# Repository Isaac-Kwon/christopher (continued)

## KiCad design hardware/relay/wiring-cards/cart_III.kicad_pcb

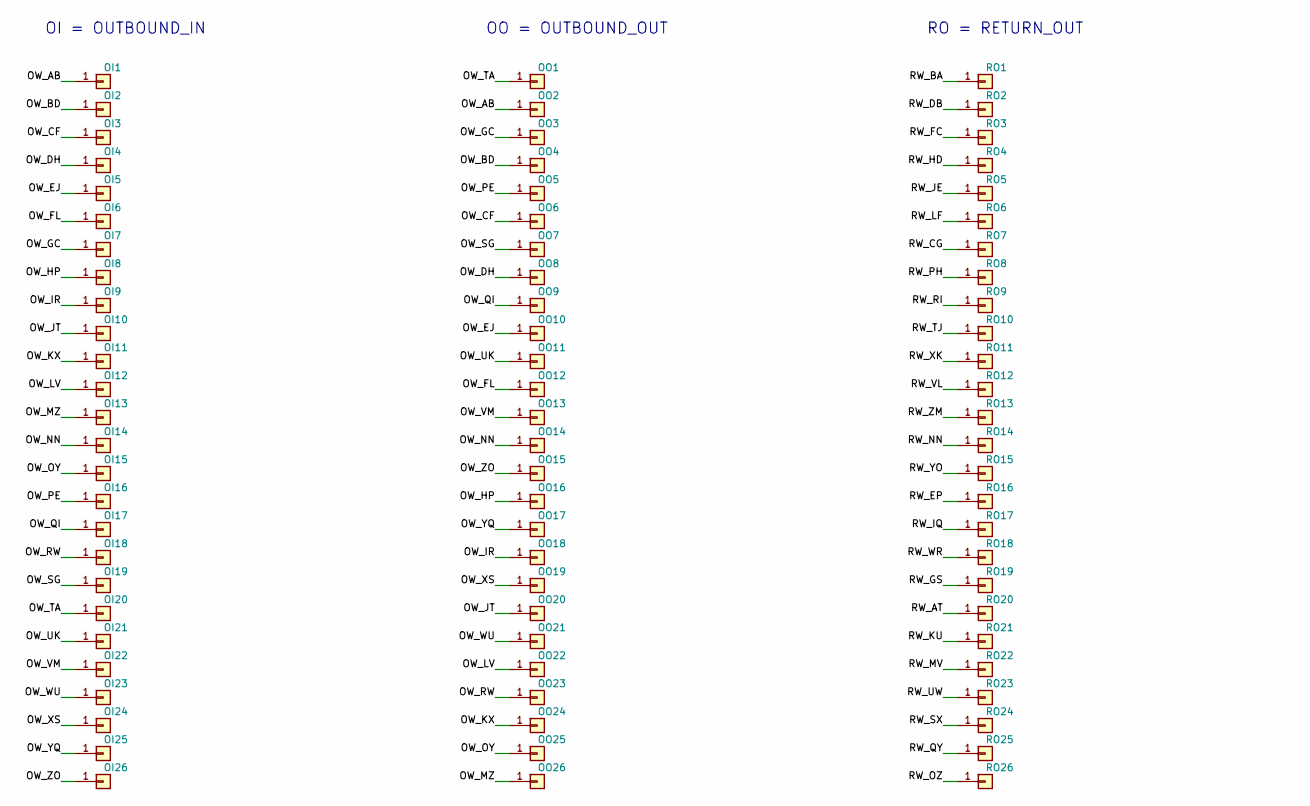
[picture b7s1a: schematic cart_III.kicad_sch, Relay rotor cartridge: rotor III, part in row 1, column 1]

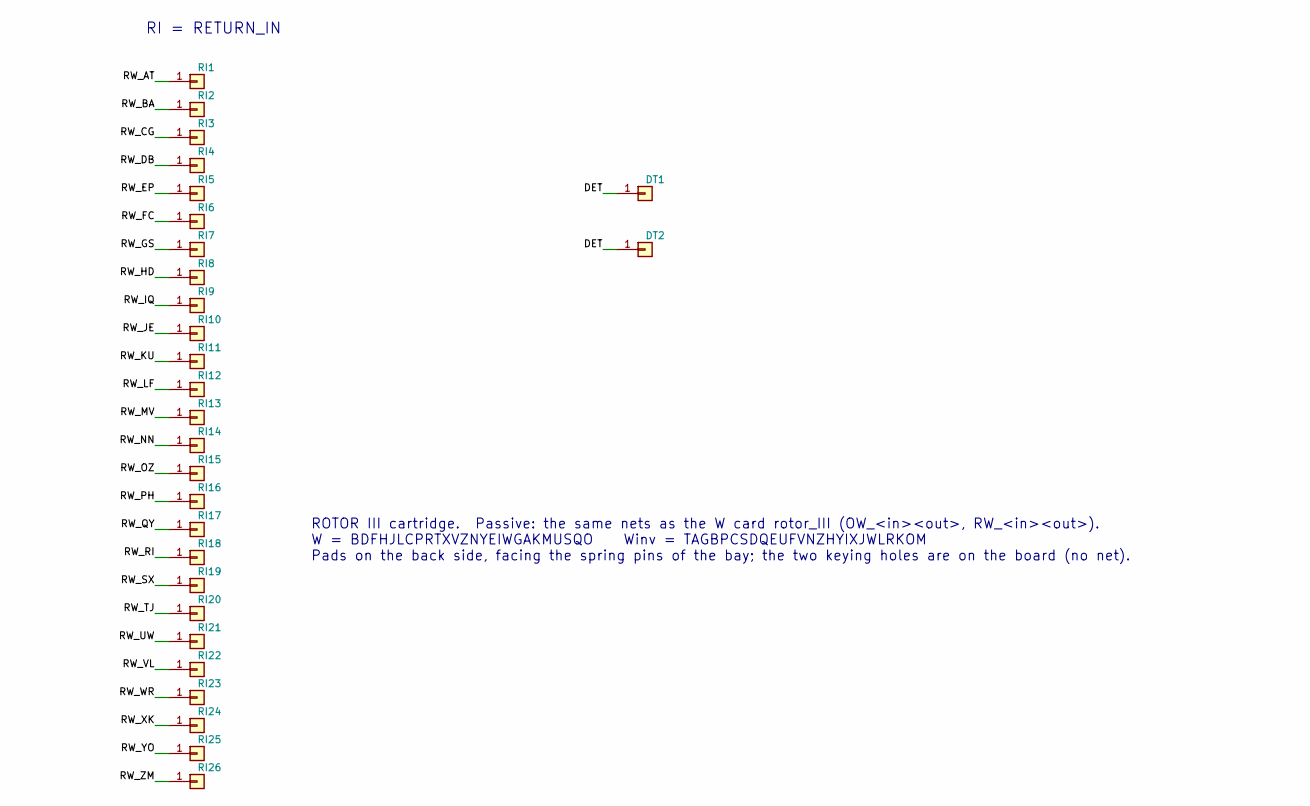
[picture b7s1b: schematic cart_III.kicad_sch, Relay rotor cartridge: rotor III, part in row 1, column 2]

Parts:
DT1: DETECT 1; CartridgePad_D1.8
DT2: DETECT 2; CartridgePad_D1.8
OI1: PAD OI A; CartridgePad_D1.8
OI2: PAD OI B; CartridgePad_D1.8
OI3: PAD OI C; CartridgePad_D1.8
OI4: PAD OI D; CartridgePad_D1.8
OI5: PAD OI E; CartridgePad_D1.8
OI6: PAD OI F; CartridgePad_D1.8
OI7: PAD OI G; CartridgePad_D1.8
OI8: PAD OI H; CartridgePad_D1.8
OI9: PAD OI I; CartridgePad_D1.8
OI10: PAD OI J; CartridgePad_D1.8
OI11: PAD OI K; CartridgePad_D1.8
OI12: PAD OI L; CartridgePad_D1.8
OI13: PAD OI M; CartridgePad_D1.8
OI14: PAD OI N; CartridgePad_D1.8
OI15: PAD OI O; CartridgePad_D1.8
OI16: PAD OI P; CartridgePad_D1.8
OI17: PAD OI Q; CartridgePad_D1.8
OI18: PAD OI R; CartridgePad_D1.8
OI19: PAD OI S; CartridgePad_D1.8
OI20: PAD OI T; CartridgePad_D1.8
OI21: PAD OI U; CartridgePad_D1.8
OI22: PAD OI V; CartridgePad_D1.8
OI23: PAD OI W; CartridgePad_D1.8
OI24: PAD OI X; CartridgePad_D1.8
OI25: PAD OI Y; CartridgePad_D1.8
OI26: PAD OI Z; CartridgePad_D1.8
OO1: PAD OO A; CartridgePad_D1.8
OO2: PAD OO B; CartridgePad_D1.8
OO3: PAD OO C; CartridgePad_D1.8
OO4: PAD OO D; CartridgePad_D1.8
OO5: PAD OO E; CartridgePad_D1.8
OO6: PAD OO F; CartridgePad_D1.8
OO7: PAD OO G; CartridgePad_D1.8
OO8: PAD OO H; CartridgePad_D1.8
OO9: PAD OO I; CartridgePad_D1.8
OO10: PAD OO J; CartridgePad_D1.8
OO11: PAD OO K; CartridgePad_D1.8
OO12: PAD OO L; CartridgePad_D1.8
OO13: PAD OO M; CartridgePad_D1.8
OO14: PAD OO N; CartridgePad_D1.8
OO15: PAD OO O; CartridgePad_D1.8
OO16: PAD OO P; CartridgePad_D1.8
OO17: PAD OO Q; CartridgePad_D1.8
OO18: PAD OO R; CartridgePad_D1.8
OO19: PAD OO S; CartridgePad_D1.8
OO20: PAD OO T; CartridgePad_D1.8
OO21: PAD OO U; CartridgePad_D1.8
OO22: PAD OO V; CartridgePad_D1.8
OO23: PAD OO W; CartridgePad_D1.8
OO24: PAD OO X; CartridgePad_D1.8
OO25: PAD OO Y; CartridgePad_D1.8
OO26: PAD OO Z; CartridgePad_D1.8
RI1: PAD RI A; CartridgePad_D1.8
RI2: PAD RI B; CartridgePad_D1.8
RI3: PAD RI C; CartridgePad_D1.8
RI4: PAD RI D; CartridgePad_D1.8
RI5: PAD RI E; CartridgePad_D1.8
RI6: PAD RI F; CartridgePad_D1.8
RI7: PAD RI G; CartridgePad_D1.8
RI8: PAD RI H; CartridgePad_D1.8
RI9: PAD RI I; CartridgePad_D1.8
RI10: PAD RI J; CartridgePad_D1.8
RI11: PAD RI K; CartridgePad_D1.8
RI12: PAD RI L; CartridgePad_D1.8
RI13: PAD RI M; CartridgePad_D1.8
RI14: PAD RI N; CartridgePad_D1.8
RI15: PAD RI O; CartridgePad_D1.8
RI16: PAD RI P; CartridgePad_D1.8
RI17: PAD RI Q; CartridgePad_D1.8
RI18: PAD RI R; CartridgePad_D1.8
RI19: PAD RI S; CartridgePad_D1.8
RI20: PAD RI T; CartridgePad_D1.8
RI21: PAD RI U; CartridgePad_D1.8
RI22: PAD RI V; CartridgePad_D1.8
RI23: PAD RI W; CartridgePad_D1.8
RI24: PAD RI X; CartridgePad_D1.8
RI25: PAD RI Y; CartridgePad_D1.8
RI26: PAD RI Z; CartridgePad_D1.8
RO1: PAD RO A; CartridgePad_D1.8
RO2: PAD RO B; CartridgePad_D1.8
RO3: PAD RO C; CartridgePad_D1.8
RO4: PAD RO D; CartridgePad_D1.8
RO5: PAD RO E; CartridgePad_D1.8
RO6: PAD RO F; CartridgePad_D1.8
RO7: PAD RO G; CartridgePad_D1.8
RO8: PAD RO H; CartridgePad_D1.8
RO9: PAD RO I; CartridgePad_D1.8
RO10: PAD RO J; CartridgePad_D1.8
RO11: PAD RO K; CartridgePad_D1.8
RO12: PAD RO L; CartridgePad_D1.8
RO13: PAD RO M; CartridgePad_D1.8
RO14: PAD RO N; CartridgePad_D1.8
RO15: PAD RO O; CartridgePad_D1.8
RO16: PAD RO P; CartridgePad_D1.8
RO17: PAD RO Q; CartridgePad_D1.8
RO18: PAD RO R; CartridgePad_D1.8
RO19: PAD RO S; CartridgePad_D1.8
RO20: PAD RO T; CartridgePad_D1.8
RO21: PAD RO U; CartridgePad_D1.8
RO22: PAD RO V; CartridgePad_D1.8
RO23: PAD RO W; CartridgePad_D1.8
RO24: PAD RO X; CartridgePad_D1.8
RO25: PAD RO Y; CartridgePad_D1.8
RO26: PAD RO Z; CartridgePad_D1.8

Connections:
/DET: DT1.1, DT2.1
/OW_AB: OI1.1, OO2.1
/OW_BD: OI2.1, OO4.1
/OW_CF: OI3.1, OO6.1
/OW_DH: OI4.1, OO8.1
/OW_EJ: OI5.1, OO10.1
/OW_FL: OI6.1, OO12.1
/OW_GC: OI7.1, OO3.1
/OW_HP: OI8.1, OO16.1
/OW_IR: OI9.1, OO18.1
/OW_JT: OI10.1, OO20.1
/OW_KX: OI11.1, OO24.1
/OW_LV: OI12.1, OO22.1
/OW_MZ: OI13.1, OO26.1
/OW_NN: OI14.1, OO14.1
/OW_OY: OI15.1, OO25.1
/OW_PE: OI16.1, OO5.1
/OW_QI: OI17.1, OO9.1
/OW_RW: OI18.1, OO23.1
/OW_SG: OI19.1, OO7.1
/OW_TA: OI20.1, OO1.1
/OW_UK: OI21.1, OO11.1
/OW_VM: OI22.1, OO13.1
/OW_WU: OI23.1, OO21.1
/OW_XS: OI24.1, OO19.1
/OW_YQ: OI25.1, OO17.1
/OW_ZO: OI26.1, OO15.1
/RW_AT: RI1.1, RO20.1
/RW_BA: RI2.1, RO1.1
/RW_CG: RI3.1, RO7.1
/RW_DB: RI4.1, RO2.1
/RW_EP: RI5.1, RO16.1
/RW_FC: RI6.1, RO3.1
/RW_GS: RI7.1, RO19.1
/RW_HD: RI8.1, RO4.1
/RW_IQ: RI9.1, RO17.1
/RW_JE: RI10.1, RO5.1
/RW_KU: RI11.1, RO21.1
/RW_LF: RI12.1, RO6.1
/RW_MV: RI13.1, RO22.1
/RW_NN: RI14.1, RO14.1
/RW_OZ: RI15.1, RO26.1
/RW_PH: RI16.1, RO8.1
/RW_QY: RI17.1, RO25.1
/RW_RI: RI18.1, RO9.1
/RW_SX: RI19.1, RO24.1
/RW_TJ: RI20.1, RO10.1
/RW_UW: RI21.1, RO23.1
/RW_VL: RI22.1, RO12.1
/RW_WR: RI23.1, RO18.1
/RW_XK: RI24.1, RO11.1
/RW_YO: RI25.1, RO15.1
/RW_ZM: RI26.1, RO13.1

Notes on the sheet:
OI = OUTBOUND_IN
OO = OUTBOUND_OUT
RO = RETURN_OUT
RI = RETURN_IN
ROTOR III cartridge. Passive: the same nets as the W card rotor_III (OW_<in><out>, RW_<in><out>). W = BDFHJLCPRTXVZNYEIWGAKMUSQO Winv = TAGBPCSDQEUFVNZHYIXJWLRKOM Pads on the back side, facing the spring pins of the bay; the two keying holes are on the board (no net).

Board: 4 copper layers, 110 parts (106 on the bottom side), 53 nets, no tracks yet.

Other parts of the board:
K3: NPTH 3.05; NPTH_3.05mm
K4: NPTH 4.05; NPTH_4.05mm
NH1, NH2: NPTH 2.7; NPTH_2.7mm
